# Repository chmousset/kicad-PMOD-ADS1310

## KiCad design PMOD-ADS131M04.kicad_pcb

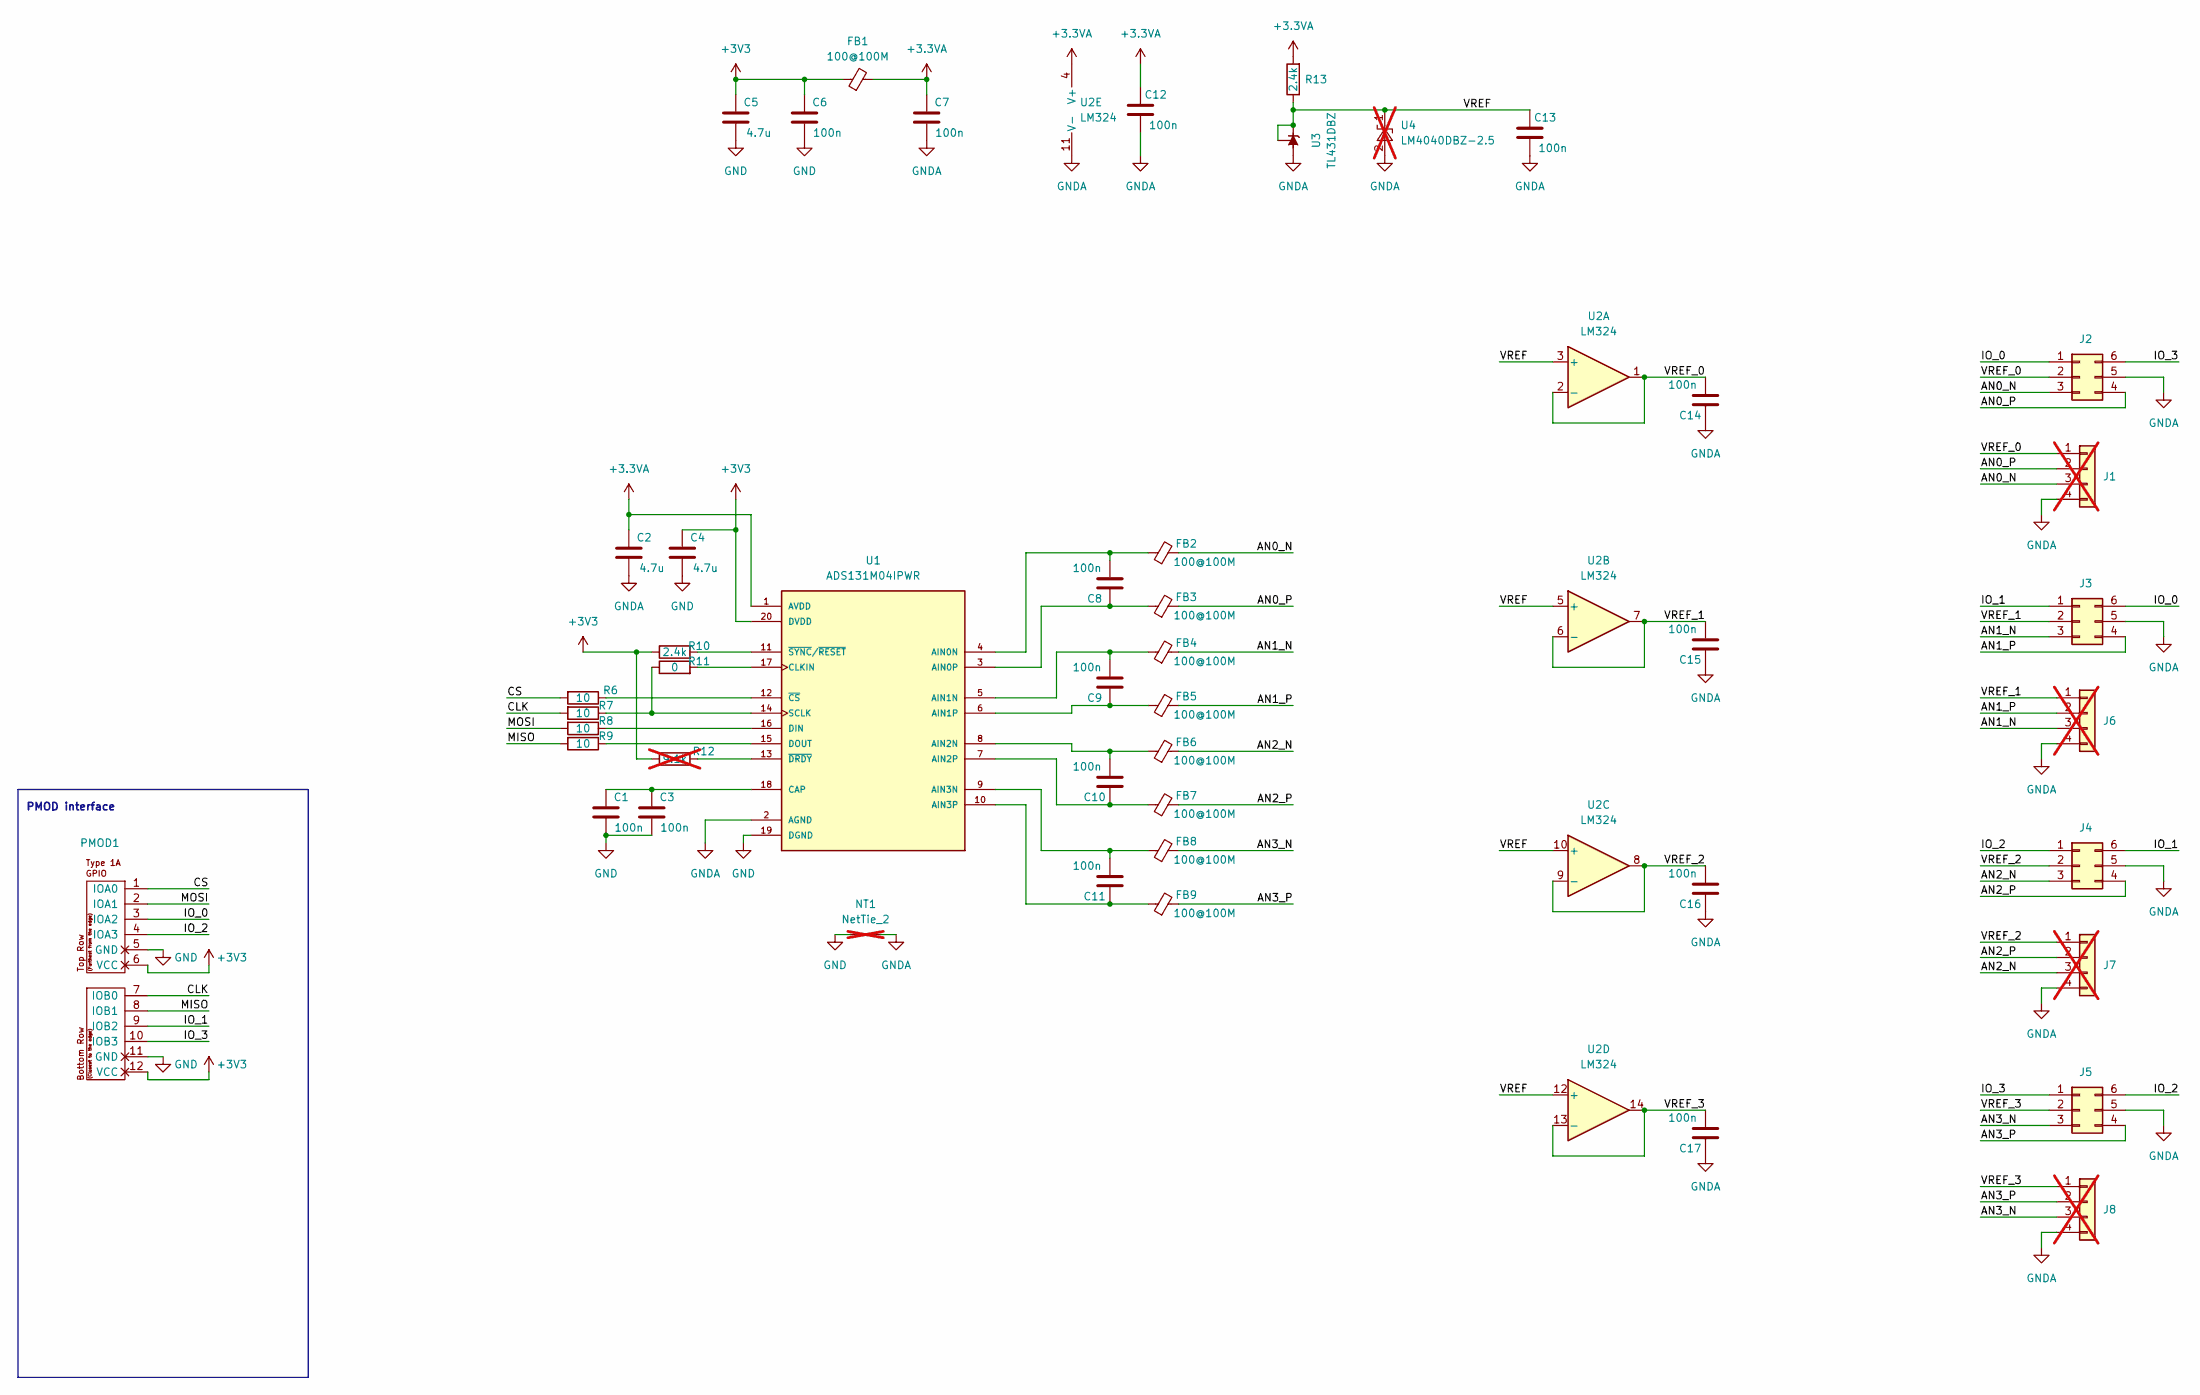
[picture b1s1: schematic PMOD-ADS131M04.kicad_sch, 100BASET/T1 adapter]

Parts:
C1, C3, C6, C7, C8, C9, C10, C11, C12, C13, C14, C15, C16, C17: 100n; C_0603_1608Metric; LCSC C14663
C2, C4, C5: 4.7u; C_0603_1608Metric; LCSC C19666
FB1, FB2, FB3, FB4, FB5, FB6, FB7, FB8, FB9: 100@100M; R_0805_2012Metric; LCSC C1015
J1, J6, J7, J8: Conn_01x03; PinHeader_1x04_P2.54mm_Vertical; not fitted
J2, J3, J4, J5: Conn_02x03_Counter_Clockwise; JST_JWPF_B06B-JWPF-SK-R_2x03_P2.00mm_Vertical
NT1: NetTie_2; NetTie-2_SMD_Pad0.5mm; not fitted
PMOD1: PMOD-Device-x2-Type-1A-GPIO; pmod_pin_array_6x2; LCSC C492434
R6, R7, R8, R9: 10; R_0603_1608Metric; LCSC C22859
R10, R13: 2.4k; R_0603_1608Metric; LCSC C22940
R11: 0; R_0603_1608Metric; LCSC C21189
R12: 9.1k; R_0603_1608Metric; LCSC C23260; not fitted
U1: ADS131M04IPWR; TSSOP-20_4.4x6.5mm_P0.65mm; PARTREV D
U2: LM324; SOIC-14_3.9x8.7mm_P1.27mm
U3: TL431DBZ; SOT-23; LCSC C3113
U4: LM4040DBZ-2.5; SOT-323_SC-70; not fitted

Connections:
+3.3VA: C2.2, C7.2, C12.2, FB1.2, R13.2, U1.1 (AVDD), U2.4 (V+)
+3V3: C4.2, C5.2, C6.2, FB1.1, PMOD1.6 (VCC), PMOD1.12 (VCC), R10.1, R12.1, U1.20 (DVDD)
/AN0_N: FB2.2, J1.3, J2.3
/AN0_P: FB3.2, J1.2, J2.4
/AN1_N: FB4.2, J3.3, J6.3
/AN1_P: FB5.2, J3.4, J6.2
/AN2_N: FB6.2, J4.3, J7.3
/AN2_P: FB7.2, J4.4, J7.2
/AN3_N: FB8.2, J5.3, J8.3
/AN3_P: FB9.2, J5.4, J8.2
/CLK: PMOD1.7 (IOB0), R7.2
/CS: PMOD1.1 (IOA0), R6.2
/IO_0: J2.1, J3.6, PMOD1.3 (IOA2)
/IO_1: J3.1, J4.6, PMOD1.9 (IOB2)
/IO_2: J4.1, J5.6, PMOD1.4 (IOA3)
/IO_3: J2.6, J5.1, PMOD1.10 (IOB3)
/MISO: PMOD1.8 (IOB1), R9.2
/MOSI: PMOD1.2 (IOA1), R8.2
/VREF: C13.2, R13.1, U2.3 (+), U2.5 (+), U2.10 (+), U2.12 (+), U3.1 (K), U3.2 (REF), U4.1 (K)
/VREF_0: C14.1, J1.1, J2.2, U2.1, U2.2 (-)
/VREF_1: C15.1, J3.2, J6.1, U2.6 (-), U2.7
/VREF_2: C16.1, J4.2, J7.1, U2.8, U2.9 (-)
/VREF_3: C17.1, J5.2, J8.1, U2.13 (-), U2.14
GND: C1.1, C3.1, C4.1, C5.1, C6.1, NT1.1, PMOD1.5 (GND), PMOD1.11 (GND), U1.19 (DGND)
GNDA: C2.1, C7.1, C12.1, C13.1, C14.2, C15.2, C16.2, C17.2, J1.4, J2.5, J3.5, J4.5, J5.5, J6.4, J7.4, J8.4, NT1.2, U1.2 (AGND), U2.11 (V-), U3.3 (A), U4.2 (A)
unnamed: C8.1, FB2.1, U1.4 (AIN0N)
unnamed: C8.2, FB3.1, U1.3 (AIN0P)
unnamed: C9.1, FB4.1, U1.5 (AIN1N)
unnamed: C9.2, FB5.1, U1.6 (AIN1P)
unnamed: C10.1, FB6.1, U1.8 (AIN2N)
unnamed: C10.2, FB7.1, U1.7 (AIN2P)
unnamed: C11.1, FB8.1, U1.9 (AIN3N)
unnamed: C11.2, FB9.1, U1.10 (AIN3P)
unnamed: C1.2, C3.2, U1.18 (CAP)
unnamed: R11.2, U1.17 (CLKIN)
unnamed: R8.1, U1.16 (DIN)
unnamed: R9.1, U1.15 (DOUT)
unnamed: R7.1, R11.1, U1.14 (SCLK)
unnamed: R6.1, U1.12 (~CS)
unnamed: R12.2, U1.13 (~DRDY)
unnamed: R10.2, U1.11 (~SYNC/~RESET)

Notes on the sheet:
PMOD interface

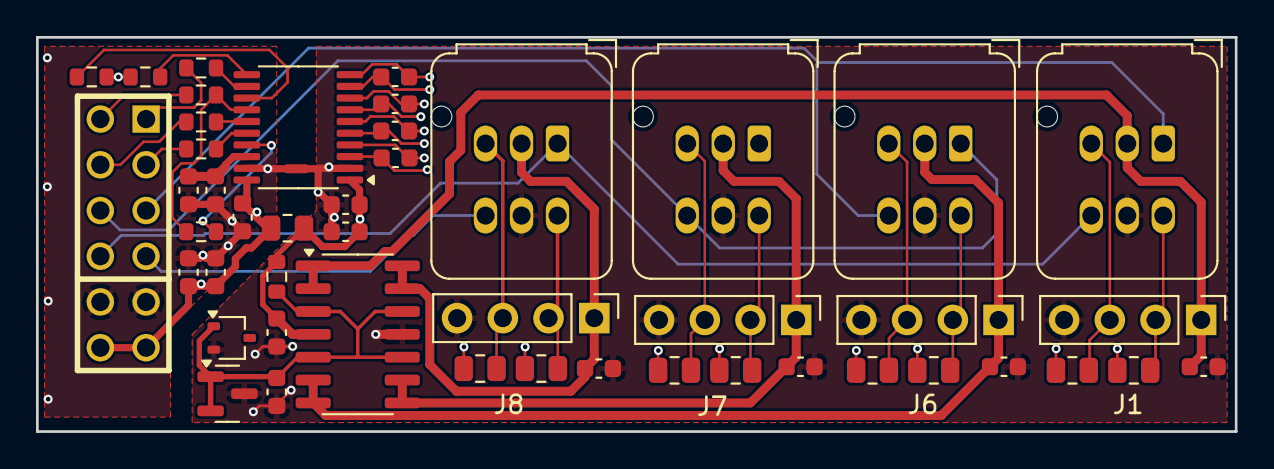
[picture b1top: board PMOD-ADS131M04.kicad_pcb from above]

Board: 4 copper layers, 66.6 x 21.9 mm, 48 parts (0 on the bottom side), 41 nets.

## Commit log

2024-04-13 [init] first version as produced
